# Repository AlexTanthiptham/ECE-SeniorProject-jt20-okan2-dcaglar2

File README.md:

# ECE445 Final Project KiCAD
## Table of Contents
- [ ] [PCBWAY-Checklist](#pcbway-checklist)
  - [ ] [Schematic](#schematic)
  - [ ] [Components](#components)
  - [ ] [Printed Circuit Board](#printed-circuit-board)
- [To Do](#to-do)
  - [x][RPI](#rpi)
  - [x][Power](#power)
  - [x][Motors](#motors)
  - [x][LIDAR](#lidar)
  - [ ][Misc](#misc)
## PCBWAY-Checklist:

Before sending your PCB design to production, make sure to go through this checklist to avoid any potential problems or errors.

### Schematic

- [x] How will you program the microcontroller? Does it have enough memory? Is it fast enough? Does the default bootloader let you program?
- [x] Are any components being overvolted? What is the maximum operating voltage of your microcontroller?
- [x] What voltage are your logic signals? Are your logic signals push/pull or open collector/drain? Do you have pull up/down resistors where needed?
- [x] Are bypass capacitors placed properly? (watch a video tutorial if needed)
- [ ] Make your circuit easy to debug! Have you placed test points on key nodes? (Add a part > search “test point”. Edit symbol properties and select a footprint. Search “test point” in the footprint editor)
- [ ] If you are apprehensive about a chip not working, you can break out the pins into a row of headers (Search “Conn” in “Choose Symbol” window)
- [ ] Do you have a low-pass filter in front of any ADCs you are using? Even if you aren’t sure you need one, make one anyway. You can bridge over the resistor and remove the capacitor if you change your mind later.
- [ ] Have an external oscillator for the micro if you have timing requirements (either strict timing, or need timing over a long period of time). Also, know exactly what oscillator requirements your microcontroller needs
- [ ] Is there an easy way to power the circuit with a lab bench power supply? Having the ability to current limit your circuit while building and testing it is very useful. This can be as simple as having test points to solder leads to.

### Components

- [ ] Are connectors used OK for rated current? Take a look at “screw terminals” for external connections.
- [ ] Are barrel connectors correctly sized? They aren’t standardized well.
- [ ] Are components hard to solder? (QFN, BGA, etc. are really hard to solder because the pads are under the package)
- [ ] Are your SMD passive components too small? 0603 imperial (not metric!) are as small as you can feasibly hand-solder. 0805 is much easier.
- [ ] Does the footprint of what you bought/will buy match what you are using on your board? Ctrl-Shift-M to measure in the KiCAD PCB Editor
- [ ] Are your components in-stock?

### Printed Circuit Board

- [ ] Bypass/decoupling capacitors are placed next to ICs
- [ ] Proper trace widths. Ask how much current will be going through. A good metric is at least 20 mils for power and at least 10 mils for signal. If they have some high current paths, they may need to be more, though. (KiCAD project window > Calculator > Trace Width Calculator)
- [ ] No 90 degree bends! These produce a lot of noise.
- [ ] The maximum size your board can be is 100mm x 100mm
- [ ] No unrouted nets, no vias in pads
- [ ] Did you include mounting holes? How will the circuit mount to the rest of your project?
- [ ] Do you have a ground plane? Ground planes help reduce EMI
- [ ] Have you entered PCBway’s capabilities in the design rule checker? (6 mil minimum trace width/trace spacing; 0.3mm minimum hole size) (In PCB Editor File > Board Setup > Design Rules > Constraints
- [ ] Have you run a design rules check (DRC)?
- [ ] Do you know
## To Do:
### RPI:
- [x] Look into USB-C power delivery protocol for RPI connector
  - Maybe we should use just a connector and not usb-c
- [x] Add UART for pi Connector
- [x] Connect labels to MCU
### Power:
- [x] Look into power subsystem required battery connections (Capacitor, resistors)
- [x] Add decouple cap for power
- [x] Connect labels to MCU
- [x] Figure out how to power mcu
- [x] Kinect Power Connector
- [x] Battery Power Connector
### Motors:
- [x] Add symbol for Motor Controller Connector
- [x] Add labels
- [x] Motor power pin symb.
- [x] Stepper motor controller Connector (needs to be discussed)
  - Should we micro step? 
  - do we just want the bare minimum? 
  - Should we be safe? -> Use a 9 way connector
- [x] Connect labels to MCU
- [x] Motor output
- [x] Motor driver IC added 
- [x] Change the Motor adapter six pins for the encoder 
- [x] figure out how to connect encoder to the pcb
### LIDAR:
- [x] Add connector for lidar
- [x] Connect labels to MCU
### Misc:
- [x ] Find missing KiCAD part symbols/models (Listed on schematic)
- [x] How to attach programmer to mcu
  - NRST Pin
- [x] Programmer connector
- [x] Add pinout for free pins for debugging(OPT)
- [ ] Add LED to check power (OPT)
- [x] Connect caps closer. 
- [x] Find footprint for motor controller
- [ ] Check breakout sizing with the pcb
- [ ] Check board connections and power pins
- [x] Fix remaining warnings
- [ ] Add pins to top side of the breakout board

## Questions:
1) What connector to use
2) Can I use usb-c as UART and power at the same time
3) 
## Reference Images:
### Block Diagram

### MCU :
https://www.st.com/content/ccc/resource/technical/document/datasheet/group3/c5/37/9c/1d/a6/09/4e/1a/DM00273119/files/DM00273119.pdf/jcr:content/translations/en.DM00273119.pdf

### Stepper Diagram:

### Motor Diagram:

### RPI:

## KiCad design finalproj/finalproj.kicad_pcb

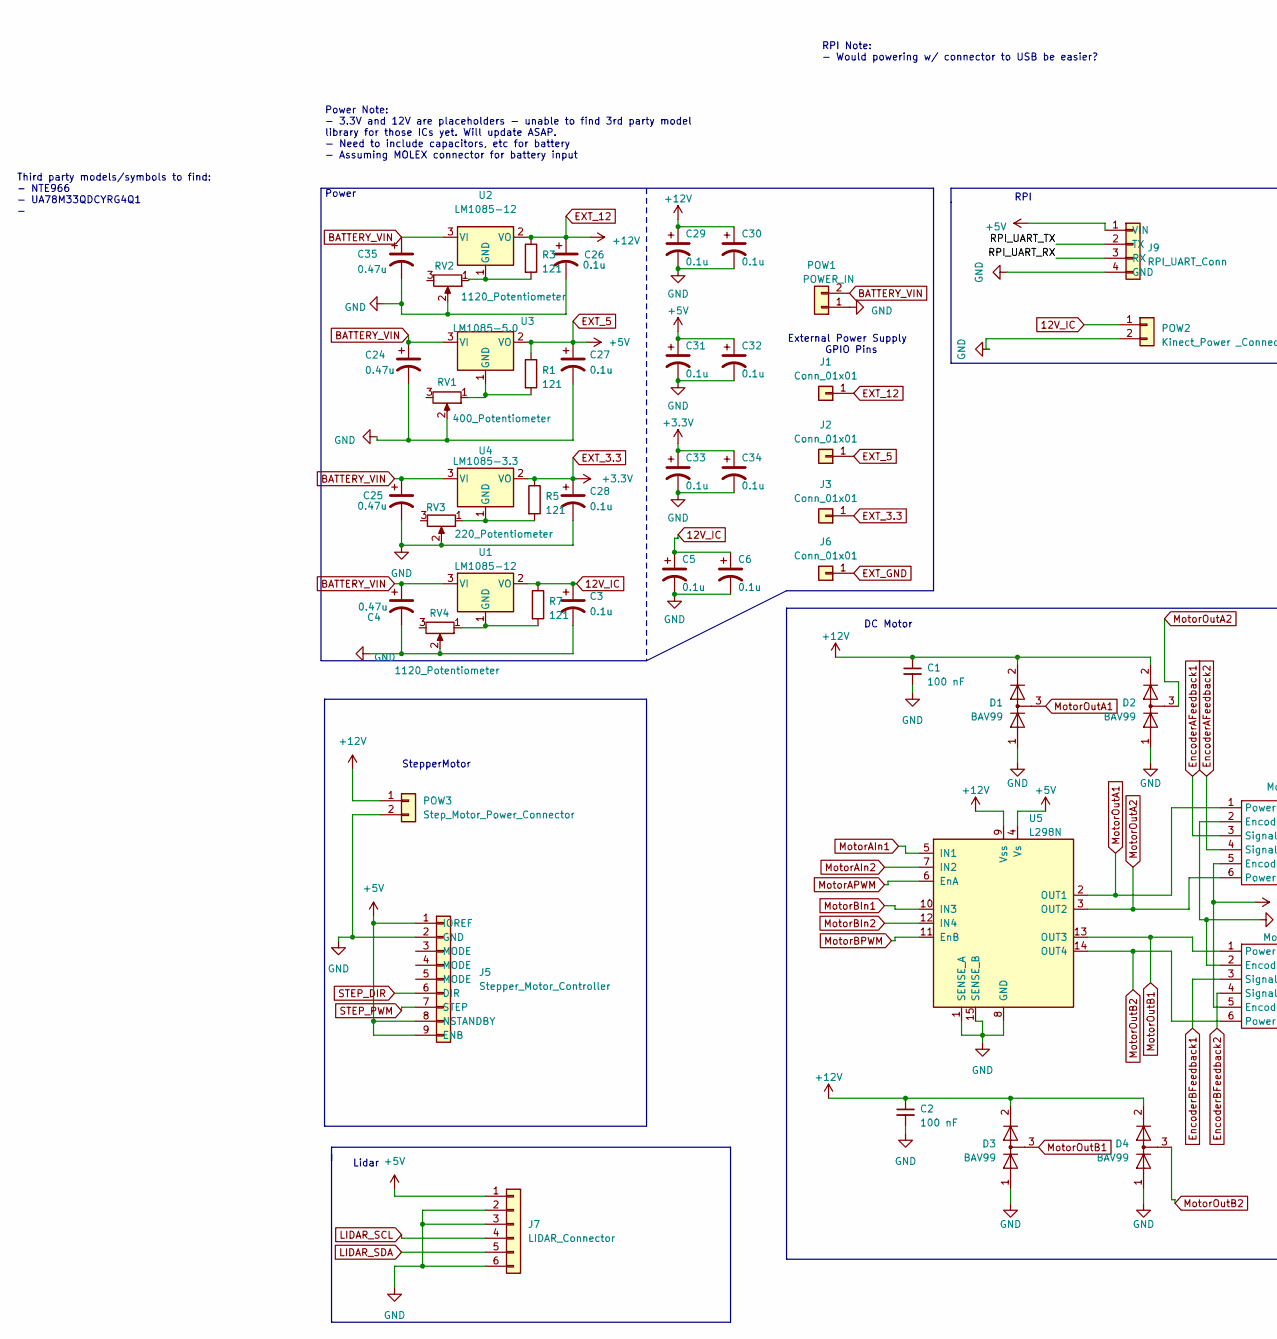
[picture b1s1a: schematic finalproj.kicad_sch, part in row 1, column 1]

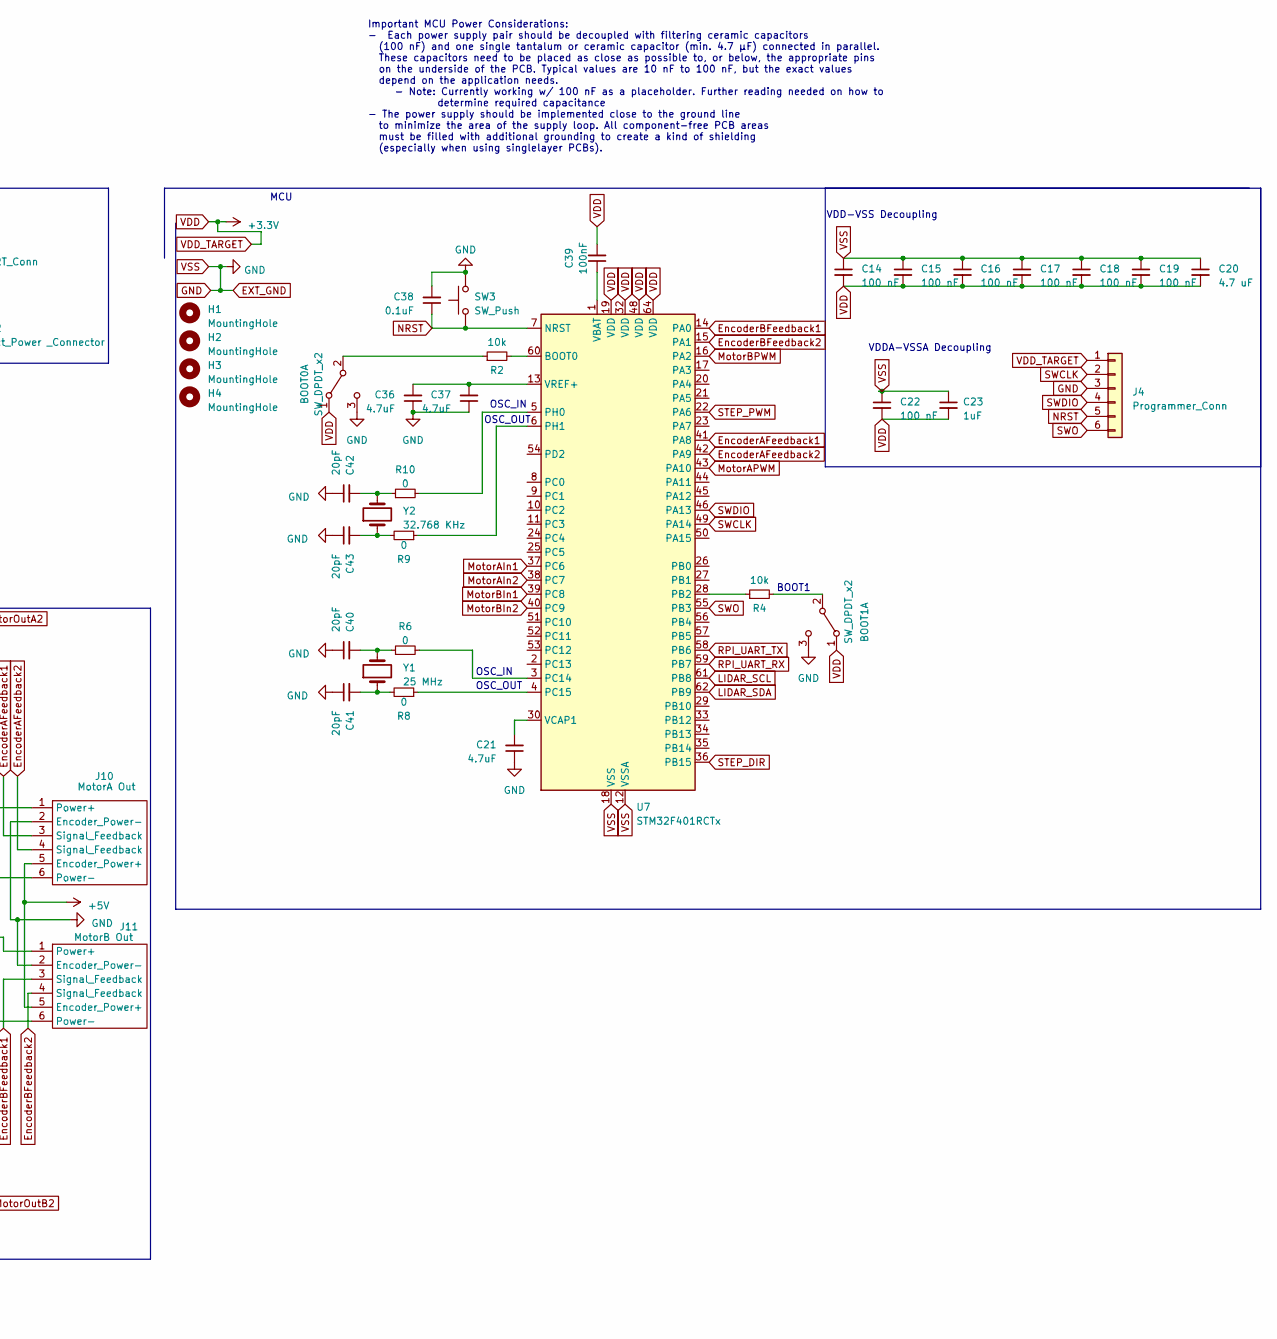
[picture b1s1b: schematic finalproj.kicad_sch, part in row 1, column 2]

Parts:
BOOT0, BOOT1: SW_DPDT_x2; SLIDE-SWITCH
C1, C2, C14, C15, C16, C17, C18, C19, C22: 100 nF; C_0805_2012Metric
C3, C5, C6, C26, C27, C28, C29, C30, C31, C32, C33, C34: 0.1u; C_0805_2012Metric
C4, C24, C25, C35: 0.47u; C_0805_2012Metric
C20: 4.7 uF; C_0805_2012Metric
C21, C36, C37: 4.7uF; C_0805_2012Metric
C23: 1uF; C_0805_2012Metric
C38: 0.1uF; C_0805_2012Metric
C39: 100nF; C_0805_2012Metric
C40, C41, C42, C43: 20pF; C_0805_2012Metric
D1, D2, D3, D4: BAV99; SOT-23
H1, H2, H3, H4: MountingHole; MountingHole_3.2mm_M3
J1, J2, J3, J6: Conn_01x01; PinHeader_1x01_P2.54mm_Vertical
J4: Programmer_Conn; PinHeader_1x06_P2.54mm_Vertical
J5: Stepper_Motor_Controller; TerminalBlock_Phoenix_PT-1,5-9-3.5-H_1x09_P3.50mm_Horizontal
J7: LIDAR_Connector; PinHeader_1x06_P2.54mm_Vertical
J9: RPI_UART_Conn; PinHeader_1x04_P2.54mm_Vertical
J10: MotorA Out; TerminalBlock_Phoenix_PT-1,5-6-3.5-H_1x06_P3.50mm_Horizontal
J11: MotorB Out; TerminalBlock_Phoenix_PT-1,5-6-3.5-H_1x06_P3.50mm_Horizontal
POW1: POWER_IN; AMASS_XT60PB-M
POW2: Kinect_Power _Connector; TerminalBlock_Phoenix_PT-1,5-2-3.5-H_1x02_P3.50mm_Horizontal
POW3: Step_Motor_Power_Connector; TerminalBlock_Phoenix_PT-1,5-2-3.5-H_1x02_P3.50mm_Horizontal
R1, R3, R5, R7: 121; R_1206_3216Metric_Pad1.30x1.75mm_HandSolder
R2, R4: 10k; R_1206_3216Metric_Pad1.30x1.75mm_HandSolder
R6, R8, R9, R10: 0; R_1206_3216Metric_Pad1.30x1.75mm_HandSolder
RV1: 400_Potentiometer; Potentiometer_Bourns_TC33X_Vertical
RV2, RV4: 1120_Potentiometer; Potentiometer_Bourns_TC33X_Vertical
RV3: 220_Potentiometer; Potentiometer_Bourns_TC33X_Vertical
SW3: SW_Push; SW_PUSH_6mm
U1, U2: LM1085-12; TO254P1054X470X1955-3
U3: LM1085-5.0; TO254P1054X470X1955-3
U4: LM1085-3.3; TO254P1054X470X1955-3
U5: L298N; TO-220-15_P2.54x2.54mm_StaggerOdd_Lead4.58mm_Vertical
U7: STM32F401RCTx; LQFP-64_10x10mm_P0.5mm
Y1: 25 MHz; XTAL_ABLS-25.000MHZ-B2F-T
Y2: 32.768 KHz; Crystal_SMD_3215-2Pin_3.2x1.5mm

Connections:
12V_IC: C3.1, C5.1, C6.1, POW2.1 (VIN), R7.1, U1.2 (VO)
BATTERY_VIN: C4.1, C24.1, C25.1, C35.1, POW1.2, U1.3 (VI), U2.3 (VI), U3.3 (VI), U4.3 (VI)
EXT_3.3: BOOT0.1 (A), BOOT1.1 (A), C14.2, C15.2, C16.2, C17.2, C18.2, C19.2, C20.2, C22.2, C23.2, C28.1, C33.1, C34.1, C39.2, J3.1, J4.1, R5.1, U4.2 (VO), U7.19 (VDD), U7.32 (VDD), U7.48 (VDD), U7.64 (VDD)
EXT_5: C27.1, C31.1, C32.1, J2.1, J5.1 (IOREF), J5.8 (NSTANDBY), J5.9 (ENB), J7.1 (POWER_IN), J9.1 (VIN), J10.5 (Encoder_Power+), J11.5 (Encoder_Power+), R1.1, U3.2 (VO), U5.4 (Vs)
EXT_12: C1.1, C2.1, C26.1, C29.1, C30.1, D1.2 (A), D2.2 (A), D3.2 (A), D4.2 (A), J1.1, POW3.1 (VIN), R3.1, U2.2 (VO), U5.9 (Vss)
EXT_GND: BOOT0.3 (C), BOOT1.3 (C), C1.2, C2.2, C3.2, C4.2, C5.2, C6.2, C14.1, C15.1, C16.1, C17.1, C18.1, C19.1, C20.1, C21.1, C22.1, C23.1, C24.2, C25.2, C26.2, C27.2, C28.2, C29.2, C30.2, C31.2, C32.2, C33.2, C34.2, C35.2, C36.1, C37.1, C38.2, C40.1, C41.1, C42.1, C43.1, D1.1 (K), D2.1 (K), D3.1 (K), D4.1 (K), J4.3, J5.2 (GND), J6.1, J7.2 (POWER_EN), J7.3 (MODE), J7.6 (GND), J9.4 (GND), J10.2 (Encoder_Power-), J11.2 (Encoder_Power-), POW1.1, POW2.2 (GND), POW3.2 (GND), RV1.2, RV2.2, RV3.2, RV4.2, SW3.2, U5.1 (SENSE_A), U5.8 (GND), U5.15 (SENSE_B), U7.12 (VSSA), U7.18 (VSS), U7.31 (VSS), U7.47 (VSS), U7.63 (VSS)
EncoderAFeedback1: J10.3 (Signal_Feedback), U7.41 (PA8)
EncoderAFeedback2: J10.4 (Signal_Feedback), U7.42 (PA9)
EncoderBFeedback1: J11.3 (Signal_Feedback), U7.14 (PA0)
EncoderBFeedback2: J11.4 (Signal_Feedback), U7.15 (PA1)
LIDAR_SCL: J7.4 (SCL), U7.61 (PB8)
LIDAR_SDA: J7.5 (SDA), U7.62 (PB9)
MotorAIn1: U5.5 (IN1), U7.37 (PC6)
MotorAIn2: U5.7 (IN2), U7.38 (PC7)
MotorAPWM: U5.6 (EnA), U7.43 (PA10)
MotorBIn1: U5.10 (IN3), U7.39 (PC8)
MotorBIn2: U5.12 (IN4), U7.40 (PC9)
MotorBPWM: U5.11 (EnB), U7.16 (PA2)
MotorOutA1: D1.3 (K), J10.1 (Power+), U5.2 (OUT1)
MotorOutA2: D2.3 (K), J10.6 (Power-), U5.3 (OUT2)
MotorOutB1: D3.3 (K), J11.1 (Power+), U5.13 (OUT3)
MotorOutB2: D4.3 (K), J11.6 (Power-), U5.14 (OUT4)
NRST: C38.1, J4.5, SW3.1, U7.7 (NRST)
unnamed: BOOT0.2 (B), R2.1
unnamed: BOOT1.2 (B), R4.2
unnamed: C40.2, R6.1, Y1.2
unnamed: C41.2, R8.2, Y1.1
unnamed: C42.2, R10.1, Y2.2
unnamed: C43.2, R9.2, Y2.1
unnamed: R7.2, RV4.1, U1.1 (GND)
unnamed: R3.2, RV2.1, U2.1 (GND)
unnamed: R1.2, RV1.1, U3.1 (GND)
unnamed: R5.2, RV3.1, U4.1 (GND)
unnamed: R2.2, U7.60 (BOOT0)
unnamed: R4.1, U7.28 (PB2)
unnamed: R6.2, U7.3 (PC14)
unnamed: R8.1, U7.4 (PC15)
unnamed: R10.2, U7.5 (PH0)
unnamed: R9.1, U7.6 (PH1)
unnamed: C39.1, U7.1 (VBAT)
unnamed: C21.2, U7.30 (VCAP1)
unnamed: C36.2, C37.2, U7.13 (VREF+)
RPI_UART_RX: J9.3 (RX), U7.59 (PB7)
RPI_UART_TX: J9.2 (TX), U7.58 (PB6)
STEP_DIR: J5.6 (DIR), U7.36 (PB15)
STEP_PWM: J5.7 (STEP), U7.22 (PA6)
SWCLK: J4.2, U7.49 (PA14)
SWDIO: J4.4, U7.46 (PA13)
SWO: J4.6, U7.55 (PB3)

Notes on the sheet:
OSC_OUT
RPI
DC Motor
MCU
Power
RPI Note: - Would powering w/ connector to USB be easier?
Lidar
Power Note: - 3.3V and 12V are placeholders - unable to find 3rd party model library for those ICs yet. Will update ASAP. - Need to include capacitors, etc for battery - Assuming MOLEX connector for battery input
OSC_IN
External Power Supply GPIO Pins
Third party models/symbols to find: - NTE966 - UA78M33QDCYRG4Q1 -
VDDA-VSSA Decoupling
BOOT1
StepperMotor
VDD-VSS Decoupling
Important MCU Power Considerations: - Each power supply pair should be decoupled with filtering ceramic capacitors (100 nF) and one single tantalum or ceramic capacitor (min. 4.7 μF) connected in parallel. These capacitors need to be placed as close as possible to, or below, the appropriate pins on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

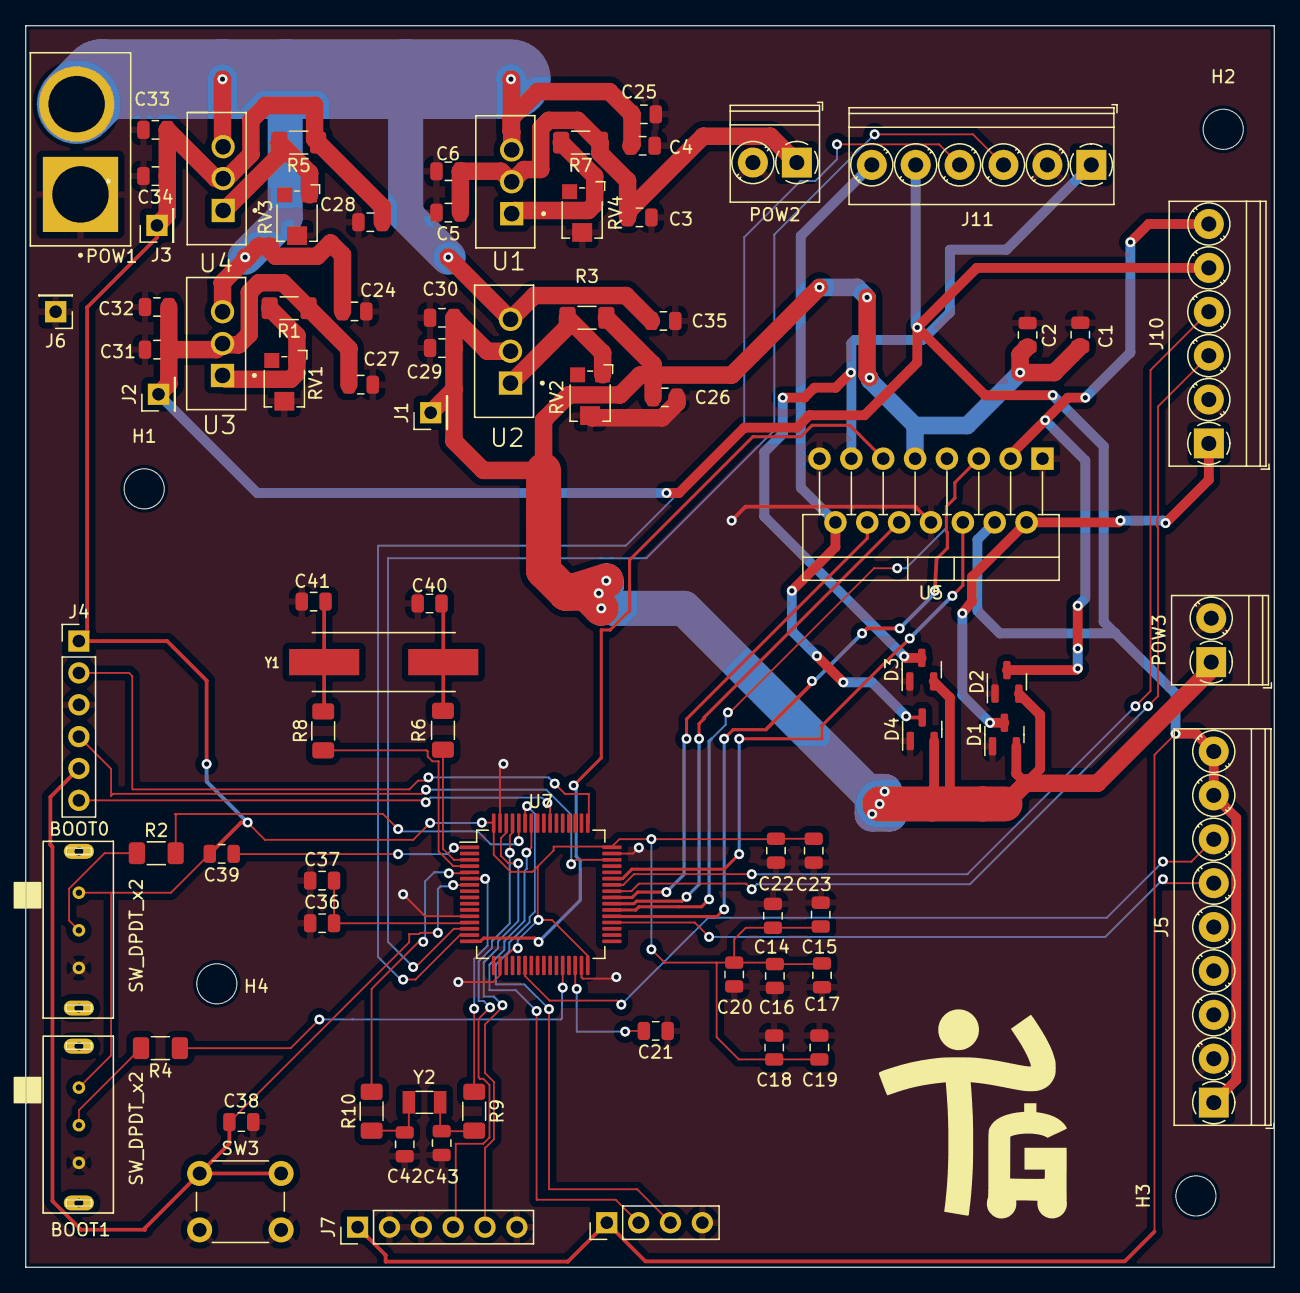
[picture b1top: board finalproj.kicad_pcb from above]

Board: 2 copper layers, 99.6 x 99.0 mm, 82 parts (0 on the bottom side), 49 nets.

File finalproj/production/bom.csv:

Designator,Footprint,Quantity,Value,LCSC Part #
"12V, 12V_IC",TO254P1054X470X1955-3,2,LM1085-12,
3.3V,TO254P1054X470X1955-3,1,LM1085-3.3,
5V,TO254P1054X470X1955-3,1,LM1085-5.0,
"BOOT0, BOOT1",SLIDE-SWITCH,2,SW_DPDT_x2,
"C1, C14, C15, C16, C17, C18, C19, C2, C22",0805,9,100 nF,
C20,0805,1,4.7 uF,
"C21, C36, C37",0805,3,4.7uF,
C23,0805,1,1uF,
"C24, C25, C35, C4",0805,4,0.47u,
"C26, C27, C28, C29, C3, C30, C31, C32, C33, C34, C5, C6",0805,12,0.1u,
C38,0805,1,0.1uF,
C39,0805,1,100nF,
"C40, C41, C42, C43",0805,4,20pF,
"D1, D2, D3, D4",SOT-23,4,BAV99,
"H1, H2, H3, H4",MountingHole_3.2mm_M3,4,MountingHole,
"J1, J2, J3, J6",PinHeader_1x01_P2.54mm_Vertical,4,Conn_01x01,
J10,"TerminalBlock_Phoenix_PT-1,5-6-3.5-H_1x06_P3.50mm_Horizontal",1,MotorA Out,
J11,"TerminalBlock_Phoenix_PT-1,5-6-3.5-H_1x06_P3.50mm_Horizontal",1,MotorB Out,
J4,PinHeader_1x06_P2.54mm_Vertical,1,Programmer_Conn,
J5,"TerminalBlock_Phoenix_PT-1,5-9-3.5-H_1x09_P3.50mm_Horizontal",1,Stepper_Motor_Controller,
J7,PinHeader_1x06_P2.54mm_Vertical,1,LIDAR_Connector,
J9,PinHeader_1x04_P2.54mm_Vertical,1,RPI_UART_Conn,
POW1,AMASS_XT60PB-M,1,POWER_IN,
POW2,"TerminalBlock_Phoenix_PT-1,5-2-3.5-H_1x02_P3.50mm_Horizontal",1,Kinect_Power _Connector,
POW3,"TerminalBlock_Phoenix_PT-1,5-2-3.5-H_1x02_P3.50mm_Horizontal",1,Step_Motor_Power_Connector,
"R1, R3, R5, R7",1206,4,121,
"R10, R6, R8, R9",1206,4,0,
"R2, R4",1206,2,10k,
RV1,Potentiometer_Bourns_TC33X_Vertical,1,400_Potentiometer,
"RV2, RV4",Potentiometer_Bourns_TC33X_Vertical,2,1120_Potentiometer,
RV3,Potentiometer_Bourns_TC33X_Vertical,1,220_Potentiometer,
SW3,SW_PUSH_6mm,1,SW_Push,
U5,TO-220-15_P2.54x2.54mm_StaggerOdd_Lead4.58mm_Vertical,1,L298N,
U7,LQFP-64_10x10mm_P0.5mm,1,STM32F401RCTx,
Y1,XTAL_ABLS-25.000MHZ-B2F-T,1,25 MHz,
Y2,Crystal_SMD_3215-2Pin_3.2x1.5mm,1,32.768 KHz,

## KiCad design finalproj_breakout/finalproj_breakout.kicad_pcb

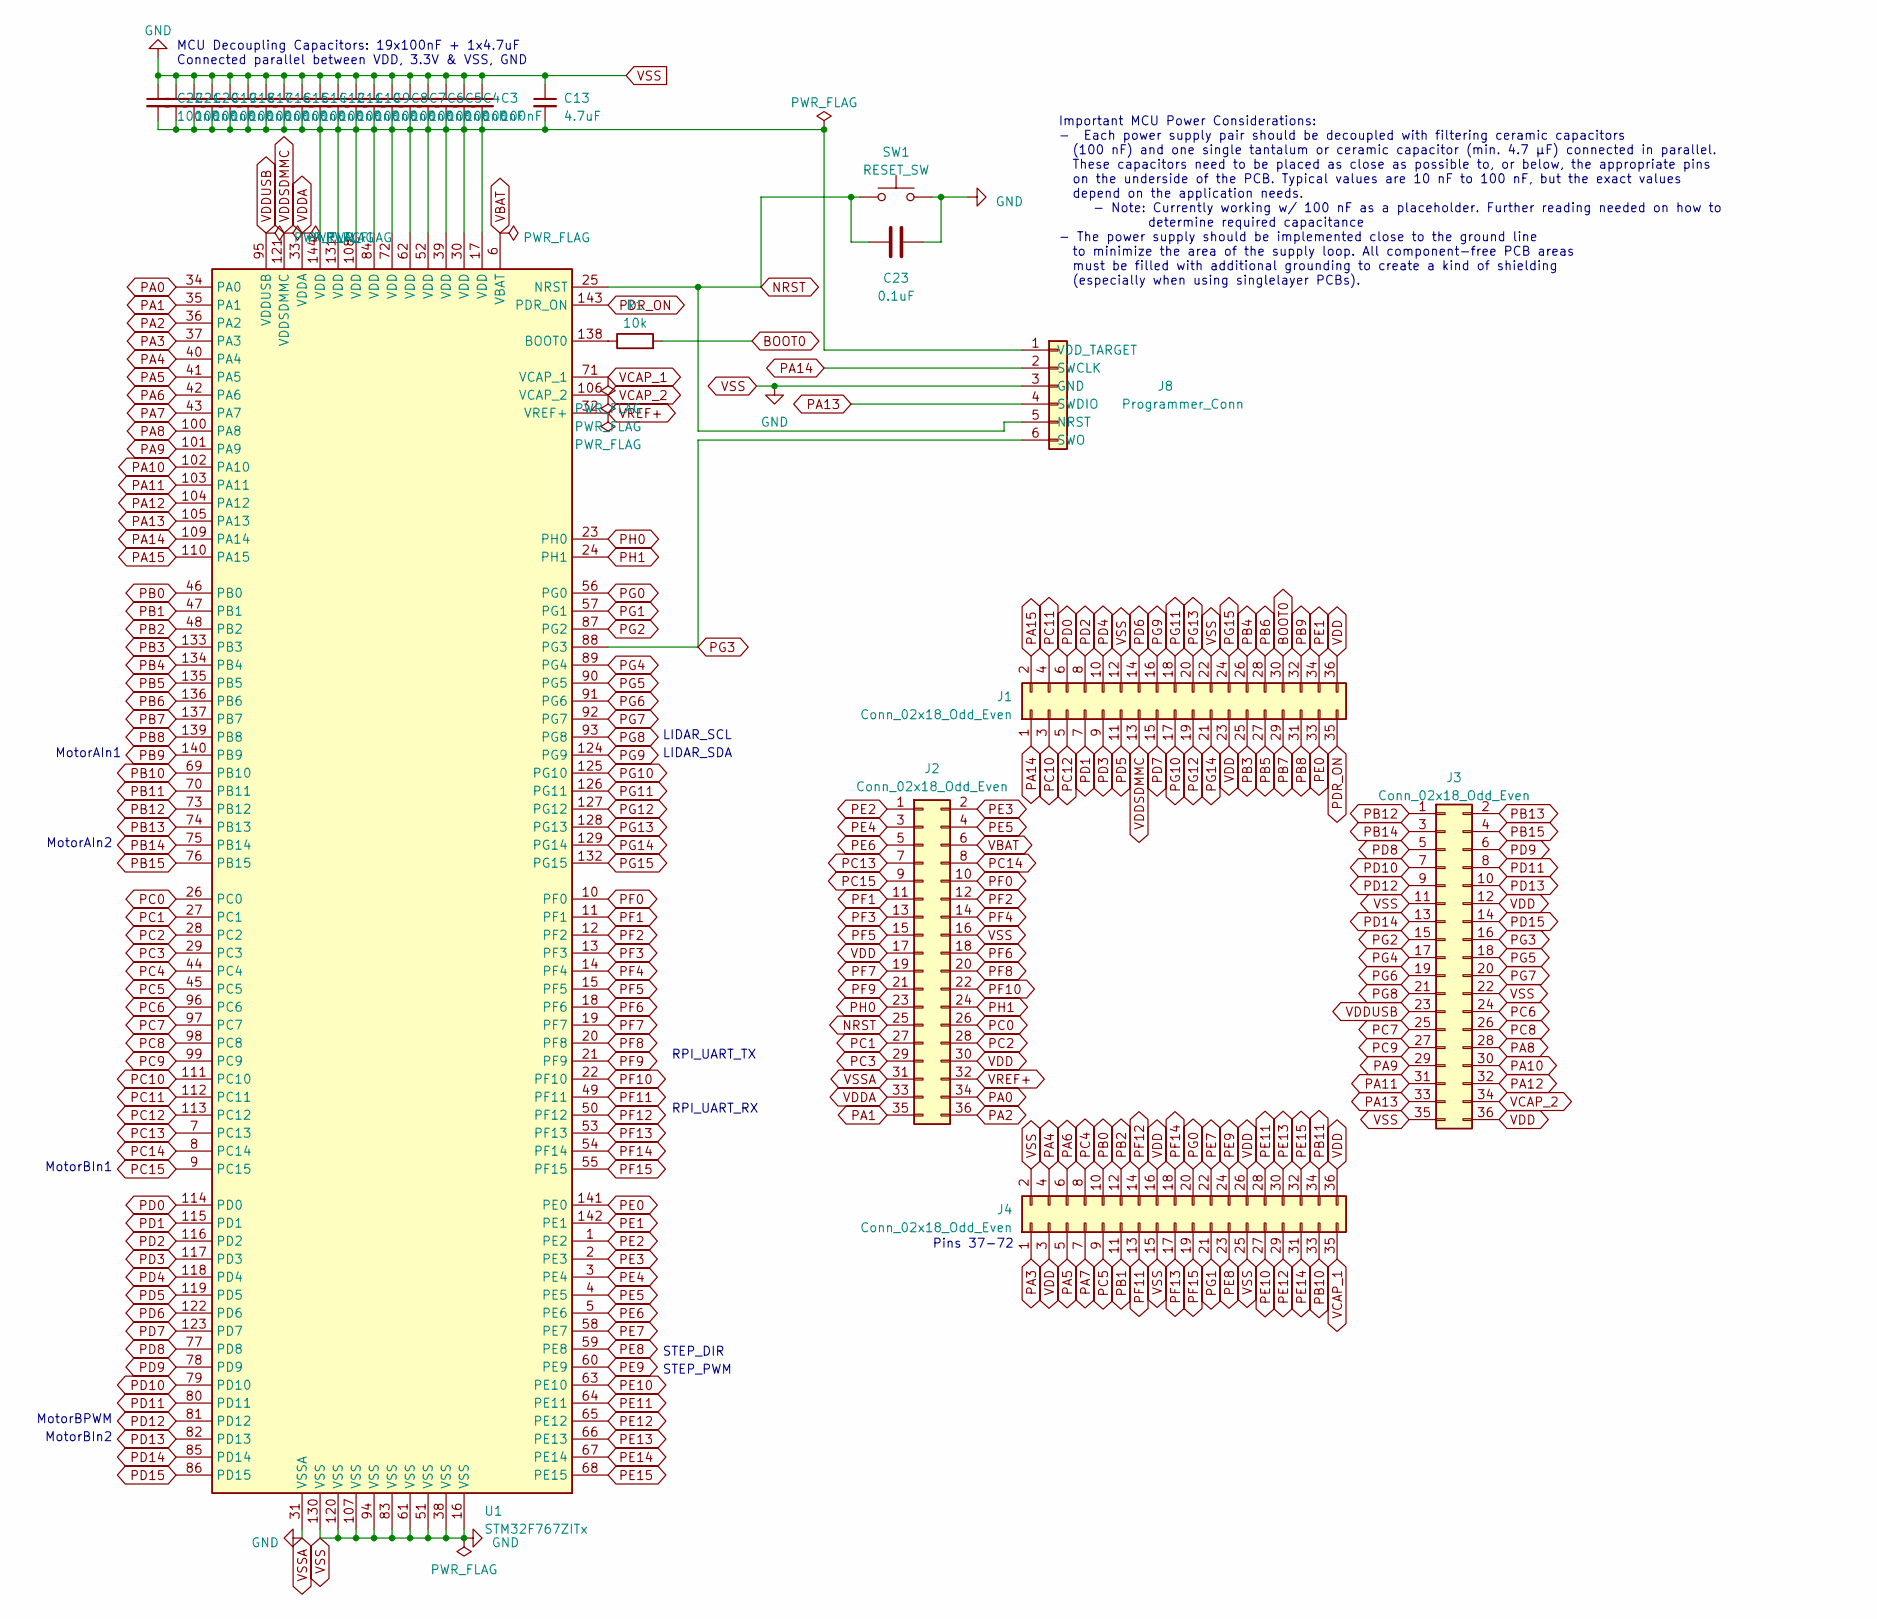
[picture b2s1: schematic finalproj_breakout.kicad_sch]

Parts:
C3, C4, C5, C6, C7, C8, C9, C10, C11, C12, C14, C15, C16, C17, C18, C19, C20, C21, C22: 100nF; C_1812_4532Metric_Pad1.57x3.40mm_HandSolder
C13: 4.7uF; C_1812_4532Metric_Pad1.57x3.40mm_HandSolder
C23: 0.1uF; C_1812_4532Metric_Pad1.57x3.40mm_HandSolder
J1, J2, J3, J4: Conn_02x18_Odd_Even; PinHeader_2x18_P2.54mm_Vertical
J8: Programmer_Conn; PinHeader_1x06_P2.54mm_Vertical
R1: 10k; R_2816_7142Metric_Pad3.20x4.45mm_HandSolder
SW1: RESET_SW; SW_PUSH_6mm
U1: STM32F767ZITx; LQFP-144_20x20mm_P0.5mm

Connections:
BOOT0: J1.30, R1.2
NRST: C23.1, J2.25, J8.5 (NRST), SW1.1, U1.25 (NRST)
unnamed: C3.2, C4.2, C5.2, C6.2, C7.2, C8.2, C9.2, C10.2, C11.2, C12.2, C13.2, C14.2, C15.2, C16.2, C17.2, C18.2, C19.2, C20.2, C21.2, C22.2, J8.1 (VDD_TARGET), U1.17 (VDD), U1.30 (VDD), U1.39 (VDD), U1.52 (VDD), U1.62 (VDD), U1.72 (VDD), U1.84 (VDD), U1.108 (VDD), U1.131 (VDD), U1.144 (VDD)
unnamed: R1.1, U1.138 (BOOT0)
PA0: J2.34, U1.34 (PA0)
PA1: J2.35, U1.35 (PA1)
PA2: J2.36, U1.36 (PA2)
PA3: J4.1, U1.37 (PA3)
PA4: J4.4, U1.40 (PA4)
PA5: J4.5, U1.41 (PA5)
PA6: J4.6, U1.42 (PA6)
PA7: J4.7, U1.43 (PA7)
PA8: J3.28, U1.100 (PA8)
PA9: J3.29, U1.101 (PA9)
PA10: J3.30, U1.102 (PA10)
PA11: J3.31, U1.103 (PA11)
PA12: J3.32, U1.104 (PA12)
PA13: J3.33, J8.4 (SWDIO), U1.105 (PA13)
PA14: J1.1, J8.2 (SWCLK), U1.109 (PA14)
PA15: J1.2, U1.110 (PA15)
PB0: J4.10, U1.46 (PB0)
PB1: J4.11, U1.47 (PB1)
PB2: J4.12, U1.48 (PB2)
PB3: J1.25, U1.133 (PB3)
PB4: J1.26, U1.134 (PB4)
PB5: J1.27, U1.135 (PB5)
PB6: J1.28, U1.136 (PB6)
PB7: J1.29, U1.137 (PB7)
PB8: J1.31, U1.139 (PB8)
PB9: J1.32, U1.140 (PB9)
PB10: J4.33, U1.69 (PB10)
PB11: J4.34, U1.70 (PB11)
PB12: J3.1, U1.73 (PB12)
PB13: J3.2, U1.74 (PB13)
PB14: J3.3, U1.75 (PB14)
PB15: J3.4, U1.76 (PB15)
PC0: J2.26, U1.26 (PC0)
PC1: J2.27, U1.27 (PC1)
PC2: J2.28, U1.28 (PC2)
PC3: J2.29, U1.29 (PC3)
PC4: J4.8, U1.44 (PC4)
PC5: J4.9, U1.45 (PC5)
PC6: J3.24, U1.96 (PC6)
PC7: J3.25, U1.97 (PC7)
PC8: J3.26, U1.98 (PC8)
PC9: J3.27, U1.99 (PC9)
PC10: J1.3, U1.111 (PC10)
PC11: J1.4, U1.112 (PC11)
PC12: J1.5, U1.113 (PC12)
PC13: J2.7, U1.7 (PC13)
PC14: J2.8, U1.8 (PC14)
PC15: J2.9, U1.9 (PC15)
PD0: J1.6, U1.114 (PD0)
PD1: J1.7, U1.115 (PD1)
PD2: J1.8, U1.116 (PD2)
PD3: J1.9, U1.117 (PD3)
PD4: J1.10, U1.118 (PD4)
PD5: J1.11, U1.119 (PD5)
PD6: J1.14, U1.122 (PD6)
PD7: J1.15, U1.123 (PD7)
PD8: J3.5, U1.77 (PD8)
PD9: J3.6, U1.78 (PD9)
PD10: J3.7, U1.79 (PD10)
PD11: J3.8, U1.80 (PD11)
PD12: J3.9, U1.81 (PD12)
PD13: J3.10, U1.82 (PD13)
PD14: J3.13, U1.85 (PD14)
PD15: J3.14, U1.86 (PD15)
PDR_ON: J1.35, U1.143 (PDR_ON)
PE0: J1.33, U1.141 (PE0)
PE1: J1.34, U1.142 (PE1)
PE2: J2.1, U1.1 (PE2)
PE3: J2.2, U1.2 (PE3)
PE4: J2.3, U1.3 (PE4)
PE5: J2.4, U1.4 (PE5)
PE6: J2.5, U1.5 (PE6)
PE7: J4.22, U1.58 (PE7)
PE8: J4.23, U1.59 (PE8)
PE9: J4.24, U1.60 (PE9)
PE10: J4.27, U1.63 (PE10)
PE11: J4.28, U1.64 (PE11)
PE12: J4.29, U1.65 (PE12)
PE13: J4.30, U1.66 (PE13)
PE14: J4.31, U1.67 (PE14)
PE15: J4.32, U1.68 (PE15)
PF0: J2.10, U1.10 (PF0)
PF1: J2.11, U1.11 (PF1)
PF2: J2.12, U1.12 (PF2)
PF3: J2.13, U1.13 (PF3)
PF4: J2.14, U1.14 (PF4)
PF5: J2.15, U1.15 (PF5)
PF6: J2.18, U1.18 (PF6)
PF7: J2.19, U1.19 (PF7)
PF8: J2.20, U1.20 (PF8)
PF9: J2.21, U1.21 (PF9)
PF10: J2.22, U1.22 (PF10)
PF11: J4.13, U1.49 (PF11)
PF12: J4.14, U1.50 (PF12)
PF13: J4.17, U1.53 (PF13)
PF14: J4.18, U1.54 (PF14)
PF15: J4.19, U1.55 (PF15)
PG0: J4.20, U1.56 (PG0)
PG1: J4.21, U1.57 (PG1)
PG2: J3.15, U1.87 (PG2)
PG3: J3.16, J8.6 (SWO), U1.88 (PG3)
PG4: J3.17, U1.89 (PG4)
PG5: J3.18, U1.90 (PG5)
PG6: J3.19, U1.91 (PG6)
PG7: J3.20, U1.92 (PG7)
PG8: J3.21, U1.93 (PG8)
PG9: J1.16, U1.124 (PG9)
PG10: J1.17, U1.125 (PG10)
PG11: J1.18, U1.126 (PG11)
PG12: J1.19, U1.127 (PG12)
PG13: J1.20, U1.128 (PG13)
PG14: J1.21, U1.129 (PG14)
PG15: J1.24, U1.132 (PG15)
PH0: J2.23, U1.23 (PH0)
PH1: J2.24, U1.24 (PH1)
VBAT: J2.6, U1.6 (VBAT)
VCAP_1: J4.35, U1.71 (VCAP_1)
VCAP_2: J3.34, U1.106 (VCAP_2)
VDD: J1.23, J1.36, J2.17, J2.30, J3.12, J3.36, J4.3, J4.16, J4.26, J4.36
VDDA: J2.33, U1.33 (VDDA)
VDDSDMMC: J1.13, U1.121 (VDDSDMMC)
VDDUSB: J3.23, U1.95 (VDDUSB)
VREF+: J2.32, U1.32 (VREF+)
VSS: C3.1, C4.1, C5.1, C6.1, C7.1, C8.1, C9.1, C10.1, C11.1, C12.1, C13.1, C14.1, C15.1, C16.1, C17.1, C18.1, C19.1, C20.1, C21.1, C22.1, C23.2, J1.12, J1.22, J2.16, J2.31, J3.11, J3.22, J3.35, J4.2, J4.15, J4.25, J8.3 (GND), SW1.2, U1.16 (VSS), U1.31 (VSSA), U1.38 (VSS), U1.51 (VSS), U1.61 (VSS), U1.83 (VSS), U1.94 (VSS), U1.107 (VSS), U1.120 (VSS), U1.130 (VSS)

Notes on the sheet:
MotorBIn1
MotorBIn2
MCU Decoupling Capacitors: 19x100nF + 1x4.7uF Connected parallel between VDD, 3.3V & VSS, GND
LIDAR_SCL
MotorAIn2
RPI_UART_TX
STEP_PWM
Pins 37-72
RPI_UART_RX
LIDAR_SDA
STEP_DIR
MotorBPWM
Important MCU Power Considerations: - Each power supply pair should be decoupled with filtering ceramic capacitors (100 nF) and one single tantalum or ceramic capacitor (min. 4.7 μF) connected in parallel. These capacitors need to be placed as close as possible to, or below, the appropriate pins on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
MotorAIn1

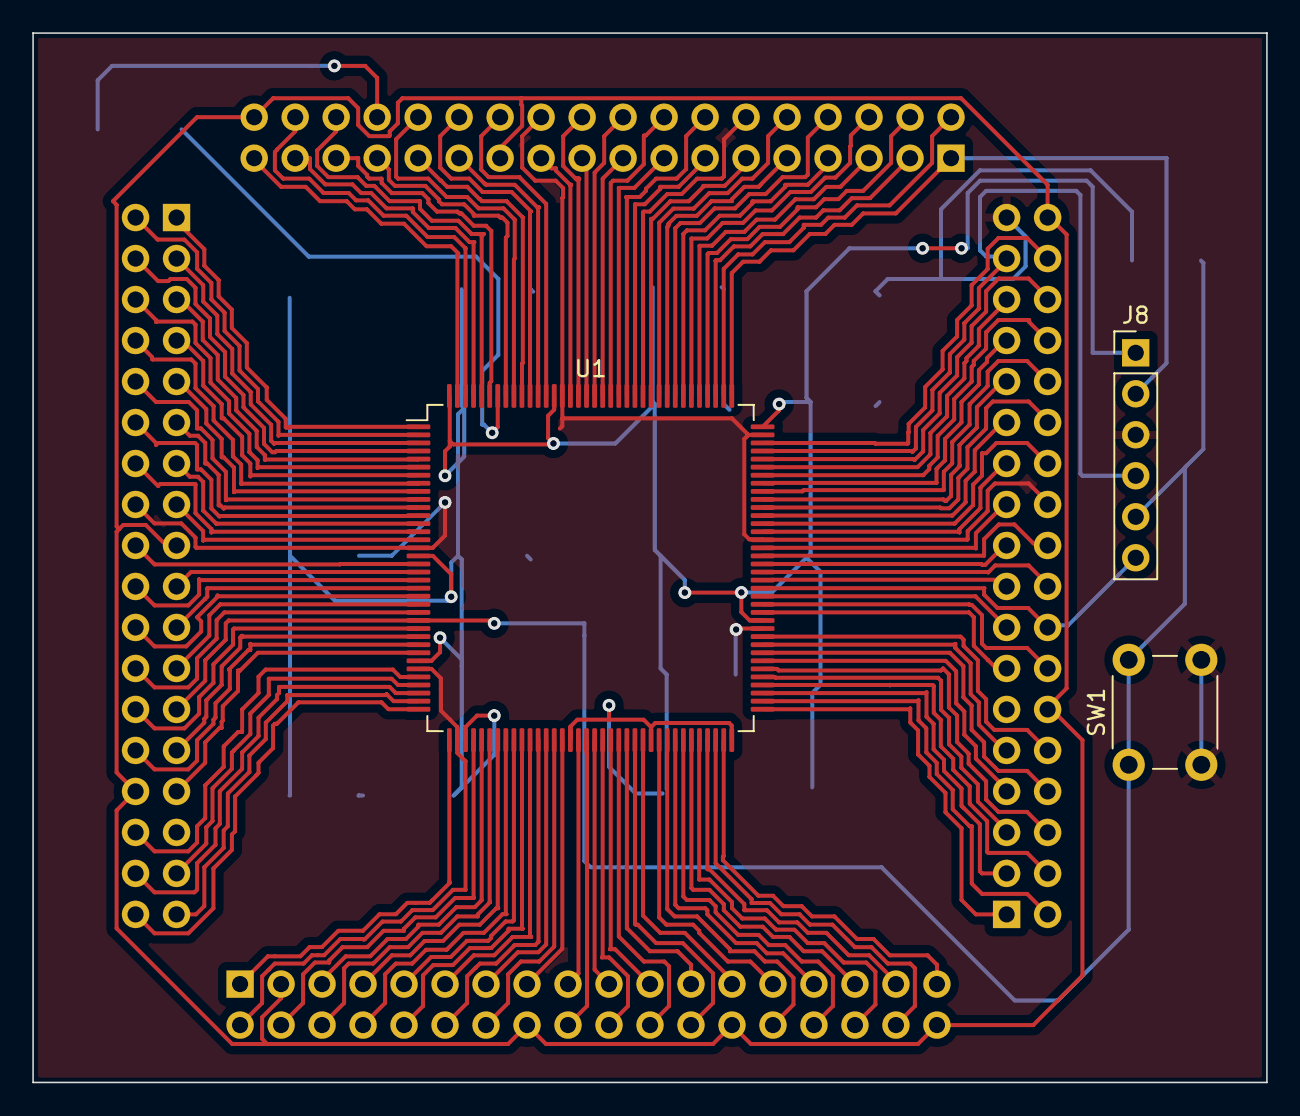
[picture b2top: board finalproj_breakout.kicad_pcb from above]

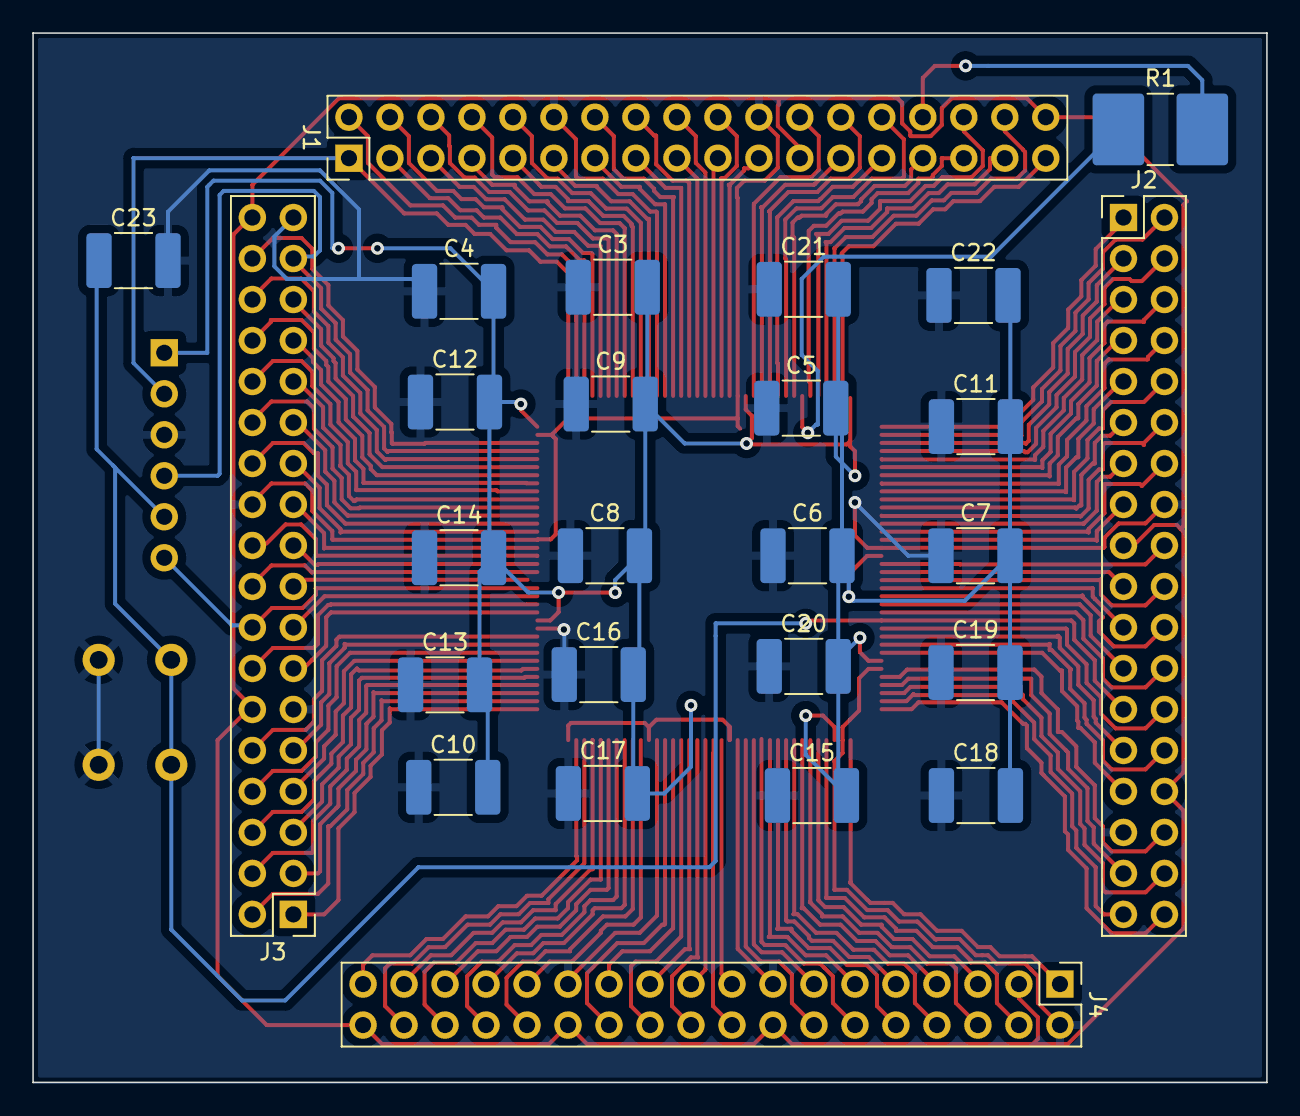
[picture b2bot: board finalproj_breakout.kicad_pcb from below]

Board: 2 copper layers, 76.5 x 65.0 mm, 29 parts (26 on the bottom side), 128 nets.

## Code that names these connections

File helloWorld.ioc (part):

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Mcu.Name=STM32F767ZITx
Mcu.Package=LQFP144
Mcu.UserName=STM32F767ZITx
PA1.GPIOParameters=GPIO_Label
PA1.GPIO_Label=RMII_REF_CLK [LAN8742A-CZ-TR_REFCLK0]
PA1.Mode=RMII
PA1.Signal=ETH_REF_CLK
PA10.GPIOParameters=GPIO_Label
PA10.GPIO_Label=USB_ID
PA10.Signal=USB_OTG_FS_ID
PA11.GPIOParameters=GPIO_Label
PA11.GPIO_Label=USB_DM
PA11.Mode=Device_Only
PA11.Signal=USB_OTG_FS_DM
PA12.GPIOParameters=GPIO_Label
PA12.GPIO_Label=USB_DP
PA12.Mode=Device_Only
PA12.Signal=USB_OTG_FS_DP
PA13.GPIOParameters=GPIO_Label
PA13.GPIO_Label=TMS
PA13.Mode=Serial_Wire
PA13.Signal=SYS_JTMS-SWDIO
PA14.GPIOParameters=GPIO_Label
PA14.GPIO_Label=TCK
PA14.Mode=Serial_Wire
PA14.Signal=SYS_JTCK-SWCLK
PA2.GPIOParameters=GPIO_Label
PA2.GPIO_Label=RMII_MDIO [LAN8742A-CZ-TR_MDIO]
PA2.Mode=RMII
PA2.Signal=ETH_MDIO
PA6.GPIOParameters=GPIO_PuPd
PA6.GPIO_PuPd=GPIO_PULLUP
PA6.Signal=S_TIM3_CH1
PA7.GPIOParameters=GPIO_Label
PA7.GPIO_Label=RMII_CRS_DV [LAN8742A-CZ-TR_CRS_DV]
PA7.Mode=RMII
PA7.Signal=ETH_CRS_DV
PA8.GPIOParameters=GPIO_Label
PA8.GPIO_Label=USB_SOF [TP1]
PA8.Mode=Activate_SOF_FS
PA8.Signal=USB_OTG_FS_SOF
PA9.GPIOParameters=GPIO_Label
PA9.GPIO_Label=USB_VBUS
PA9.Mode=Activate_VBUS
PA9.Signal=USB_OTG_FS_VBUS
PB0.GPIOParameters=GPIO_Label
PB0.GPIO_Label=LD1 [Green]
PB0.Signal=GPIO_Output
PB13.GPIOParameters=GPIO_Label
PB13.GPIO_Label=RMII_TXD1 [LAN8742A-CZ-TR_TXD1]
PB13.Mode=RMII
PB13.Signal=ETH_TXD1
PB14.GPIOParameters=GPIO_Label
PB14.GPIO_Label=LD3 [Red]
PB14.Signal=GPIO_Output
PB3.GPIOParameters=GPIO_Label
PB3.GPIO_Label=SWO
PB3.Signal=SYS_JTDO-SWO
PB6.Signal=GPIO_Output
PB7.GPIOParameters=GPIO_Label
PB7.GPIO_Label=LD2 [Blue]
PB7.Signal=GPIO_Output
PB8.GPIOParameters=GPIO_Pu
PB8.GPIO_Pu=GPIO_PULLUP
PB8.Mode=I2C
PB8.Signal=I2C1_SCL
PB9.GPIOParameters=GPIO_Pu
PB9.GPIO_Pu=GPIO_PULLUP
PB9.Mode=I2C
PB9.Signal=I2C1_SDA
PC1.GPIOParameters=GPIO_Label
PC1.GPIO_Label=RMII_MDC [LAN8742A-CZ-TR_MDC]
PC1.Mode=RMII
PC1.Signal=ETH_MDC
PC10.Mode=Asynchronous
PC10.Signal=UART4_TX
PC11.Mode=Asynchronous
PC11.Signal=UART4_RX
PC13.GPIOParameters=GPIO_Label
PC13.GPIO_Label=USER_Btn [B1]
PC13.Signal=GPXTI13
PC14/OSC32_IN.Signal=RCC_OSC32_IN
PC15/OSC32_OUT.Signal=RCC_OSC32_OUT
PC4.GPIOParameters=GPIO_Label
PC4.GPIO_Label=RMII_RXD0 [LAN8742A-CZ-TR_RXD0]
PC4.Mode=RMII
PC4.Signal=ETH_RXD0
PC5.GPIOParameters=GPIO_Label
PC5.GPIO_Label=RMII_RXD1 [LAN8742A-CZ-TR_RXD1]
PC5.Mode=RMII
PC5.Signal=ETH_RXD1
PD12.GPIOParameters=GPIO_PuPd
PD12.GPIO_PuPd=GPIO_PULLUP
PD12.Signal=S_TIM4_CH1
PD8.GPIOParameters=GPIO_Label
PD8.GPIO_Label=STLK_RX [STM32F103CBT6_PA3]
PD8.Mode=Asynchronous
PD8.Signal=USART3_TX
PD9.GPIOParameters=GPIO_Label
PD9.GPIO_Label=STLK_TX [STM32F103CBT6_PA2]
PD9.Mode=Asynchronous
PD9.Signal=USART3_RX
PE13.GPIOParameters=GPIO_PuPd,GPIO_Label
PE13.GPIO_Label=MotorBIn2
PE13.GPIO_PuPd=GPIO_PULLUP
PE13.Signal=GPIO_Output
PE9.GPIOParameters=GPIO_PuPd
PE9.GPIO_PuPd=GPIO_PULLUP
PE9.Signal=S_TIM1_CH1
PF15.GPIOParameters=GPIO_PuPd,GPIO_Label
PF15.GPIO_Label=MotorBIn1
PF15.GPIO_PuPd=GPIO_PULLUP
PF15.Signal=GPIO_Output
PG11.GPIOParameters=GPIO_Label
PG11.GPIO_Label=RMII_TX_EN [LAN8742A-CZ-TR_TXEN]
PG11.Mode=RMII
PG11.Signal=ETH_TX_EN
PG13.GPIOParameters=GPIO_Label
PG13.GPIO_Label=RMII_TXD0 [LAN8742A-CZ-TR_TXD0]
PG13.Mode=RMII
PG13.Signal=ETH_TXD0
PG14.GPIOParameters=GPIO_PuPd,GPIO_Label
PG14.GPIO_Label=MotorAIn2
PG14.GPIO_PuPd=GPIO_PULLUP
PG14.Signal=GPIO_Output
PG6.GPIOParameters=GPIO_Label
PG6.GPIO_Label=USB_PowerSwitchOn [STMPS2151STR_EN]
PG6.Signal=GPIO_Output
PG7.GPIOParameters=GPIO_Label
PG7.GPIO_Label=USB_OverCurrent [STMPS2151STR_FAULT]
PG7.Signal=GPIO_Input
PG9.GPIOParameters=GPIO_PuPd,GPIO_Label
PG9.GPIO_Label=MotorAIn1
PG9.GPIO_PuPd=GPIO_PULLUP
PG9.Signal=GPIO_Output
PH0/OSC_IN.GPIOParameters=GPIO_Label
PH0/OSC_IN.GPIO_Label=MCO [STM32F103CBT6_PA8]
PH0/OSC_IN.Mode=HSE-External-Oscillator
PH0/OSC_IN.Signal=RCC_OSC_IN
PH1/OSC_OUT.Mode=HSE-External-Oscillator
PH1/OSC_OUT.Signal=RCC_OSC_OUT
RCC.HSE_VALUE=8000000
RCC.SYSCLKFreq_VALUE=96000000
RCC.SYSCLKSource=RCC_SYSCLKSOURCE_PLLCLK
RCC.SYSCLKSourceVirtual=RCC_SYSCLKSOURCE_PLLCLK
board=NUCLEO-F767ZI
boardIOC=true

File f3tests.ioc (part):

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Mcu.Name=STM32F401R(B-C)Tx
Mcu.Package=LQFP64
Mcu.UserName=STM32F401RBTx
PA0-WKUP.GPIOParameters=GPIO_PuPd
PA0-WKUP.GPIO_PuPd=GPIO_PULLUP
PA0-WKUP.Signal=S_TIM2_CH1_ETR
PA1.GPIOParameters=GPIO_PuPd
PA1.GPIO_PuPd=GPIO_PULLUP
PA1.Signal=S_TIM2_CH2
PA10.GPIOParameters=GPIO_PuPd,GPIO_Label
PA10.GPIO_Label=MotorAPWM
PA10.GPIO_PuPd=GPIO_PULLUP
PA10.Signal=GPIO_Output
PA13.Mode=Trace_Asynchronous_SW
PA13.Signal=SYS_JTMS-SWDIO
PA14.Mode=Trace_Asynchronous_SW
PA14.Signal=SYS_JTCK-SWCLK
PA2.GPIOParameters=GPIO_Speed,GPIO_PuPd,GPIO_Label,GPIO_ModeDefaultOutputPP
PA2.GPIO_Label=MotorBPWMOutput
PA2.GPIO_ModeDefaultOutputPP=GPIO_MODE_OUTPUT_PP
PA2.GPIO_PuPd=GPIO_PULLUP
PA2.GPIO_Speed=GPIO_SPEED_FREQ_LOW
PA2.Signal=GPIO_Output
PA8.GPIOParameters=GPIO_PuPd
PA8.GPIO_PuPd=GPIO_PULLUP
PA8.Signal=S_TIM1_CH1
PA9.GPIOParameters=GPIO_PuPd
PA9.GPIO_PuPd=GPIO_PULLUP
PA9.Signal=S_TIM1_CH2
PB15.Signal=TIM1_CH3N
PB2.GPIOParameters=GPIO_Label
PB2.GPIO_Label=BOOT1
PB2.Signal=GPIO_Input
PB3.Mode=Trace_Asynchronous_SW
PB3.Signal=SYS_JTDO-SWO
PB6.GPIOParameters=GPIO_Label
PB6.GPIO_Label=RPI_TX
PB6.Mode=Asynchronous
PB6.Signal=USART1_TX
PB7.GPIOParameters=GPIO_Label
PB7.GPIO_Label=RPI_RX
PB7.Mode=Asynchronous
PB7.Signal=USART1_RX
PC6.GPIOParameters=GPIO_Label
PC6.GPIO_Label=MotorAIn1
PC6.Signal=GPIO_Output
PC7.GPIOParameters=GPIO_Label
PC7.GPIO_Label=MotorAIn2
PC7.Signal=GPIO_Output
PC8.GPIOParameters=GPIO_Label
PC8.GPIO_Label=MotorBIn1
PC8.Signal=GPIO_Output
PC9.GPIOParameters=GPIO_Label
PC9.GPIO_Label=MotorBIn2
PC9.Signal=GPIO_Output
PH0\ -\ OSC_IN.Mode=HSE-External-Oscillator
PH0\ -\ OSC_IN.Signal=RCC_OSC_IN
PH1\ -\ OSC_OUT.Mode=HSE-External-Oscillator
PH1\ -\ OSC_OUT.Signal=RCC_OSC_OUT
RCC.HSE_VALUE=25000000
RCC.SYSCLKFreq_VALUE=16000000
board=custom
